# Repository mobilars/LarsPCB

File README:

These files are my PCB designs. Some of them are also copies of other PCBs that others have made. 

License: CC-BY-SA-NC

http://creativecommons.org/licenses/by-nc-sa/3.0/

More info on http://lars.roland.bz/

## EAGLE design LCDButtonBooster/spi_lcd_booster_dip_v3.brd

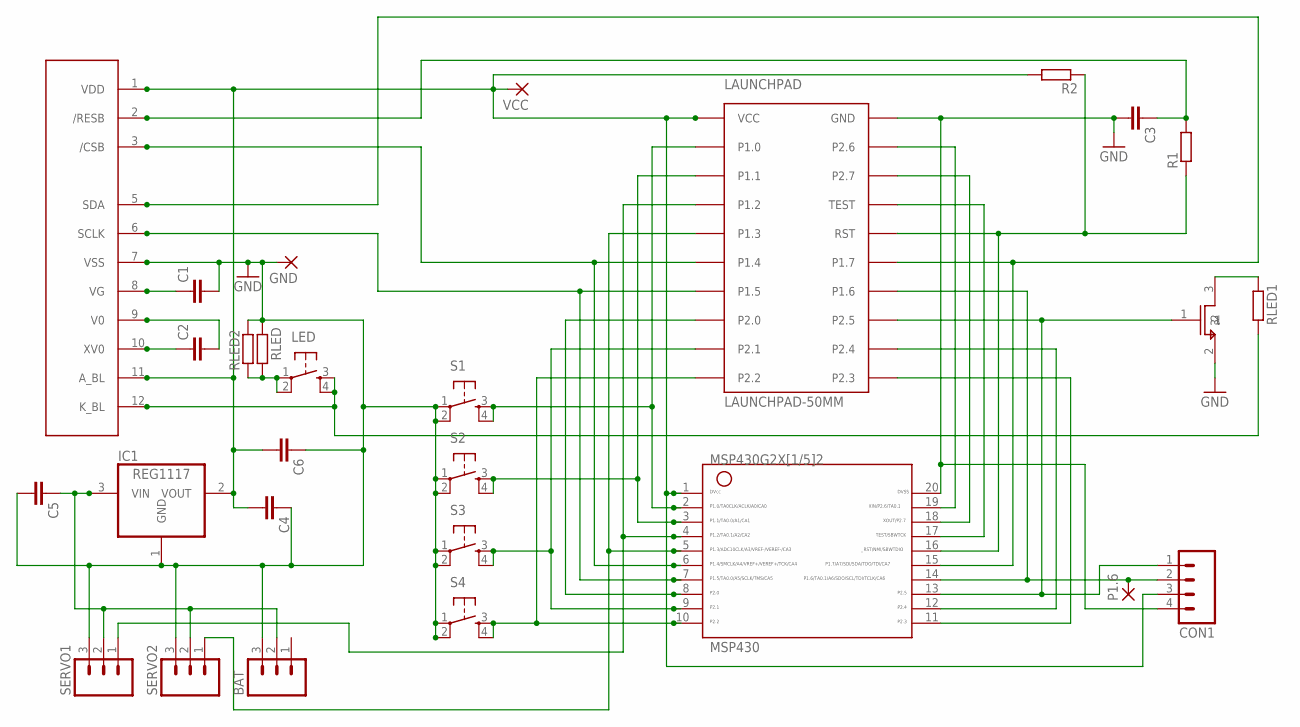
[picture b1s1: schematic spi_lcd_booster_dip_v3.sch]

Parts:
BAT: M03PTH; 1X03
C1, C2, C3, C4, C5, C6: CAP1206; 1206
CON1: M04PTH; 1X04
GND: 2,15/1,0
IC1: REG1117; SOT223
LAUNCHPAD: LAUNCHPAD-50MM
LED: TAC_SWITCHPTH; TACTILE-PTH
LEDSW: 2N7002PW; SOT323-R
MSP430: G2X[1/5]2---N20; N20
P1.6: 2,15/1,0
R1, R2: R-EU_R1206; R1206
RLED, RLED1: R-EU_R1206; R1206
RLED2: R-EU_0207/10; 0207/10
S1, S2, S3, S4: TAC_SWITCHPTH; TACTILE-PTH
SERVO1, SERVO2: M03PTH; 1X03
U$1: PE9665WRFPE9665WRF-WHOLE; PE9665WRF
VCC: 2,15/1,0

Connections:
CSB: LAUNCHPAD.P1.4, MSP430.6, U$1.3 (/CSB)
GND: BAT.3, C1.2, C3.2, C4.1, C5.2, C6.1, CON1.4, GND.1, IC1.1 (GND), LAUNCHPAD.GND, LEDSW.2, MSP430.20, RLED.1, RLED2.2, S1.1, S1.2, S2.1, S2.2, S3.1, S3.2, S4.1, S4.2, SERVO1.3, SERVO2.3, U$1.7 (VSS)
KBL: LED.3, LED.4, RLED1.2, U$1.12 (K_BL)
unnamed: C2.1, U$1.10 (XV0)
unnamed: C2.2, U$1.9 (V0)
unnamed: C1.1, U$1.8 (VG)
unnamed: LAUNCHPAD.P2.6, MSP430.19
unnamed: C3.1, R1.2, U$1.2 (/RESB)
unnamed: LAUNCHPAD.P2.7, MSP430.18
unnamed: LAUNCHPAD.RST, MSP430.16, R1.1, R2.1
unnamed: LAUNCHPAD.P1.7, MSP430.15, U$1.5 (SDA)
unnamed: LEDSW.3, RLED1.1
unnamed: LAUNCHPAD.TEST, MSP430.17
unnamed: LAUNCHPAD.P2.2, MSP430.10, S4.3, S4.4
unnamed: CON1.2, LAUNCHPAD.P1.6, MSP430.14, P1.6.1
unnamed: CON1.1, LAUNCHPAD.P2.5, LEDSW.1, MSP430.13
unnamed: LAUNCHPAD.P2.4, MSP430.12
unnamed: LAUNCHPAD.P2.3, MSP430.11
unnamed: LAUNCHPAD.P2.1, MSP430.9, S3.3, S3.4
unnamed: LAUNCHPAD.P1.5, MSP430.7, U$1.6 (SCLK)
unnamed: LAUNCHPAD.P2.0, MSP430.8
unnamed: LED.1, LED.2, RLED.2, RLED2.1
P1.0: LAUNCHPAD.P1.0, MSP430.2, S1.3, S1.4
P1.1: LAUNCHPAD.P1.1, MSP430.3, S2.3, S2.4
P1.2: LAUNCHPAD.P1.2, MSP430.4, SERVO1.1
P1.3: LAUNCHPAD.P1.3, MSP430.5, SERVO2.1
VBAT: BAT.2, C5.1, IC1.3 (VIN), SERVO1.2, SERVO2.2
VDD: C4.2, C6.2, CON1.3, IC1.2 (VOUT), LAUNCHPAD.VCC, MSP430.1, R2.2, U$1.1 (VDD), U$1.11 (A_BL), VCC.1

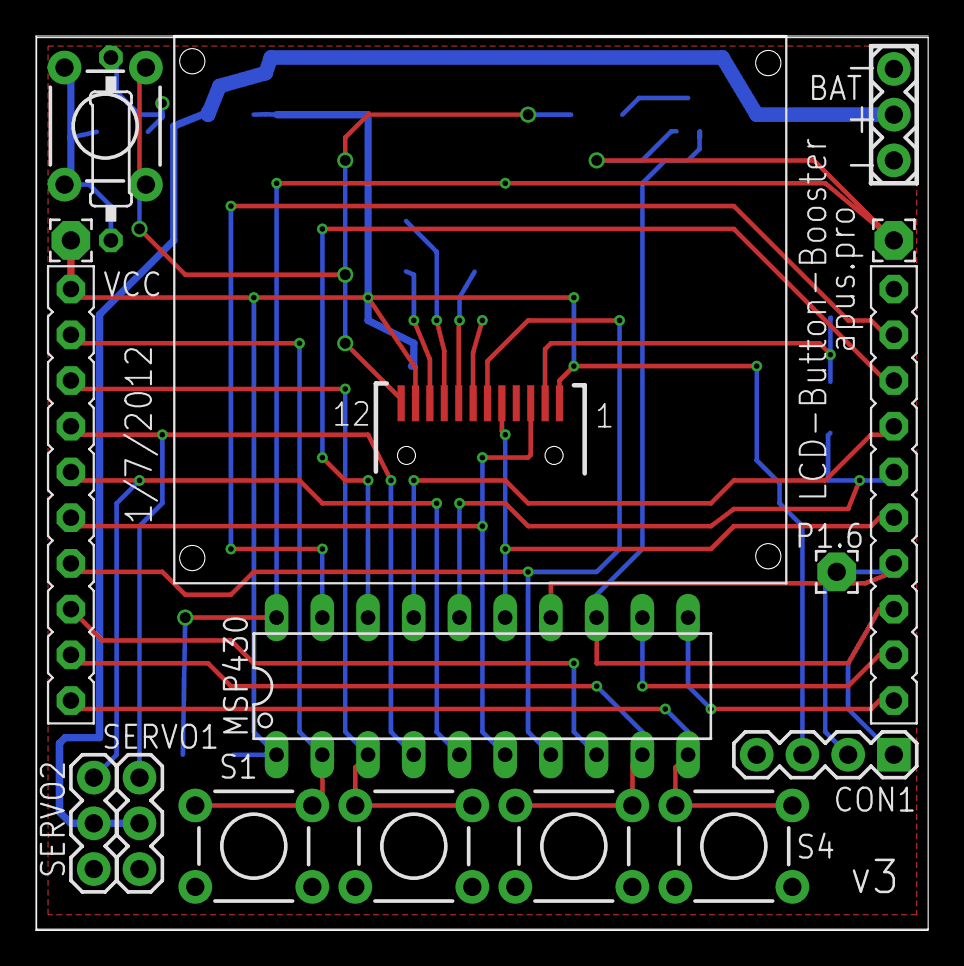
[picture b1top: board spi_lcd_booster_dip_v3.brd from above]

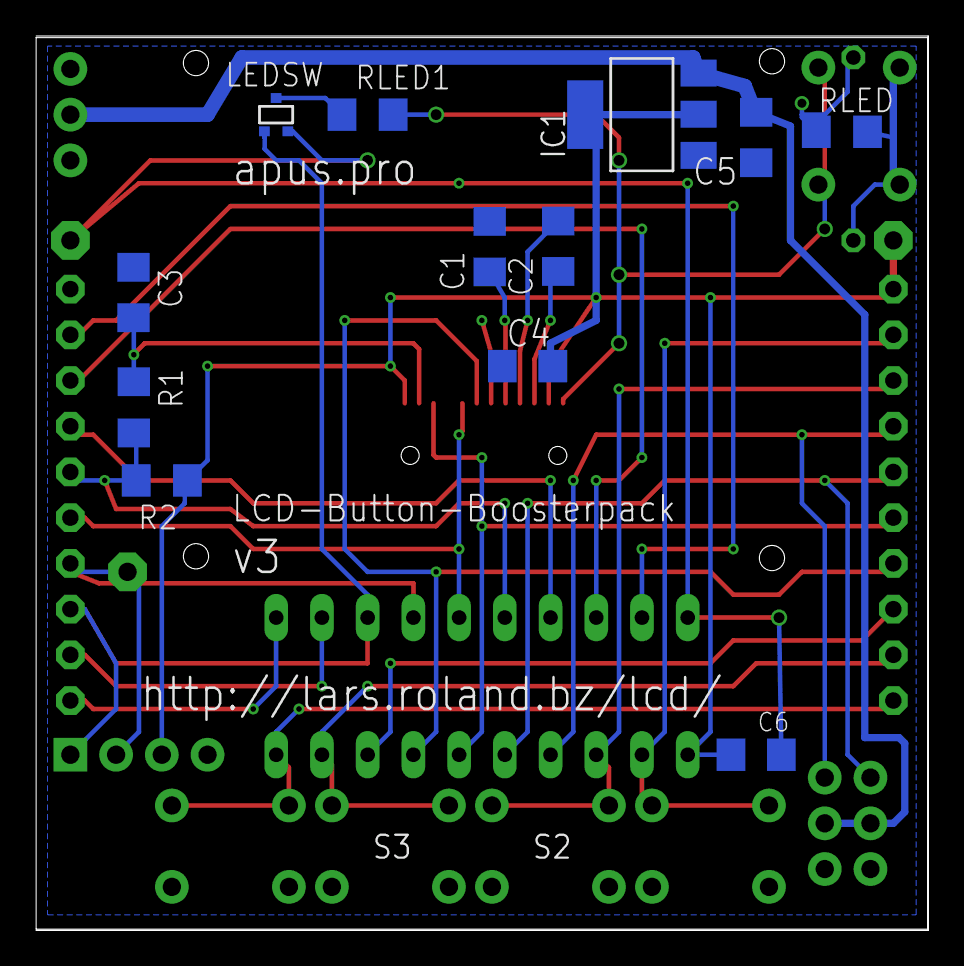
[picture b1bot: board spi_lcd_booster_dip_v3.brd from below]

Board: 2 copper layers, 49.6 x 49.7 mm, 28 parts (12 on the bottom side), 28 nets.

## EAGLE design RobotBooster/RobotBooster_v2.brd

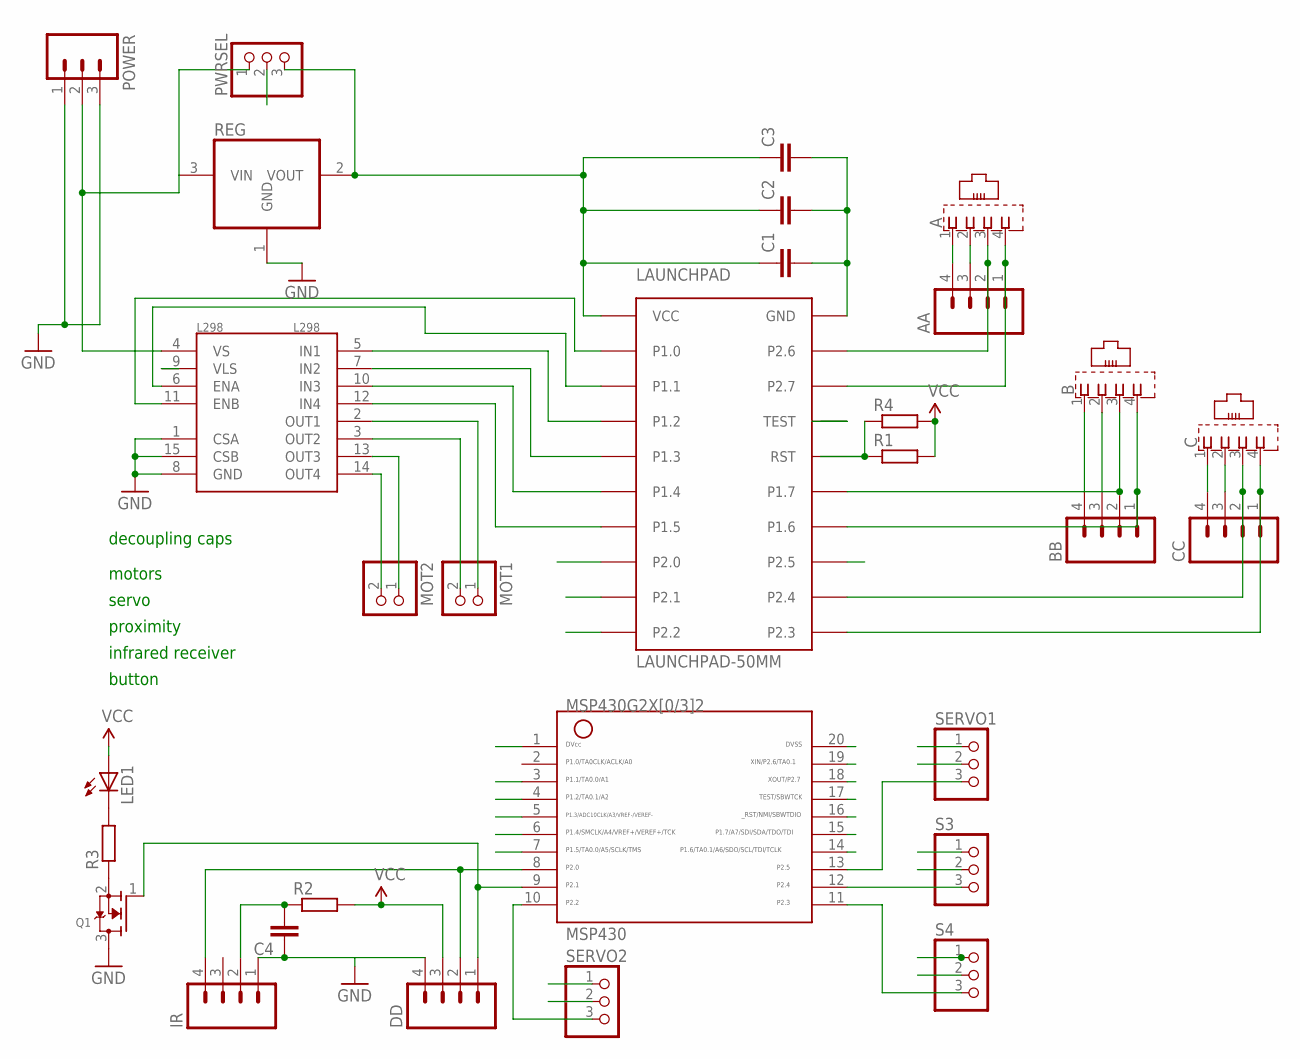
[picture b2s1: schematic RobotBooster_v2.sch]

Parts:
A: XRJK-S-01-6-4-0-9M2
AA: M04PTH; 1X04
B: XRJK-S-01-6-4-0-9M2
BB: M04PTH; 1X04
C: XRJK-S-01-6-4-0-9M2
C1, C2: C-EU025-030X050; C025-030X050
C3, C4: C-EUC1206; C1206
CC: M04PTH; 1X04
DD: M04PTH; 1X04
IR: M04PTH; 1X04
L298: L298; MULTIWATT15
LAUNCHPAD: LAUNCHPAD-50MM
LED1: LED5MM
MOT1, MOT2: PINHD-1X2; 1X02
MSP430: MSP430; N20
POWER: M03LONGPADS; 1X03_LONGPADS
PWRSEL: PINHD-1X3; 1X03
Q1: MOSFET-NREFLOW; SOT23
R1: R-EU_0207/10; 0207/10
R2, R3, R4: R-EU_R1206; R1206
REG: REG1117; SOT223
S3, S4: PINHD-1X3; 1X03
SERVO1, SERVO2: PINHD-1X3; 1X03

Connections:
GND: A.1, AA.4, B.1, BB.4, C.1, C1.2, C2.2, C3.2, C4.1, CC.4, DD.4, IR.1, L298.1 (CSA), L298.8 (GND), L298.15 (CSB), LAUNCHPAD.GND, MSP430.20, POWER.1, POWER.3, Q1.3 (D), REG.1 (GND), S3.1, S4.1, SERVO1.1, SERVO2.1
unnamed: L298.14 (OUT4), MOT2.2
unnamed: L298.13 (OUT3), MOT2.1
unnamed: L298.3 (OUT2), MOT1.2
unnamed: L298.2 (OUT1), MOT1.1
unnamed: C4.2, IR.2, R2.1
unnamed: Q1.2 (S), R3.1
unnamed: LED1.K (C), R3.2
unnamed: MSP430.13, SERVO1.3
P1.0: L298.11 (ENB), LAUNCHPAD.P1.0
P1.1: L298.6 (ENA), LAUNCHPAD.P1.1, MSP430.3
P1.2: L298.5 (IN1), LAUNCHPAD.P1.2, MSP430.4
P1.3: L298.7 (IN2), LAUNCHPAD.P1.3, MSP430.5
P1.4: L298.10 (IN3), LAUNCHPAD.P1.4, MSP430.6
P1.5: L298.12 (IN4), LAUNCHPAD.P1.5, MSP430.7
P1.6: B.4, BB.1, LAUNCHPAD.P1.6, MSP430.14
P1.7: B.3, BB.2, LAUNCHPAD.P1.7, MSP430.15
P2.0: DD.2, IR.4, LAUNCHPAD.P2.0, MSP430.8
P2.1: DD.1, LAUNCHPAD.P2.1, MSP430.9, Q1.1 (G)
P2.2: LAUNCHPAD.P2.2, MSP430.10, SERVO2.3
P2.3: C.4, CC.1, LAUNCHPAD.P2.3, MSP430.11, S4.3
P2.4: C.3, CC.2, LAUNCHPAD.P2.4, MSP430.12, S3.3
P2.5: LAUNCHPAD.P2.5
P2.6: A.3, AA.2, LAUNCHPAD.P2.6, MSP430.19
P2.7: A.4, AA.1, LAUNCHPAD.P2.7, MSP430.18
RST: LAUNCHPAD.RST, MSP430.16, R1.1, R4.1
TEST: LAUNCHPAD.TEST, MSP430.17
VBAT: L298.4 (VS), POWER.2, PWRSEL.1, REG.3 (VIN)
VCC: A.2, AA.3, B.2, BB.3, C.2, C1.1, C2.1, C3.1, CC.3, DD.3, L298.9 (VLS), LAUNCHPAD.VCC, LED1.A, MSP430.1, PWRSEL.3, R1.2, R2.2, R4.2, REG.2 (VOUT)
VSERV: PWRSEL.2, S3.2, S4.2, SERVO1.2, SERVO2.2

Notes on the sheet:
servo
proximity
infrared receiver
motors
button
decoupling caps

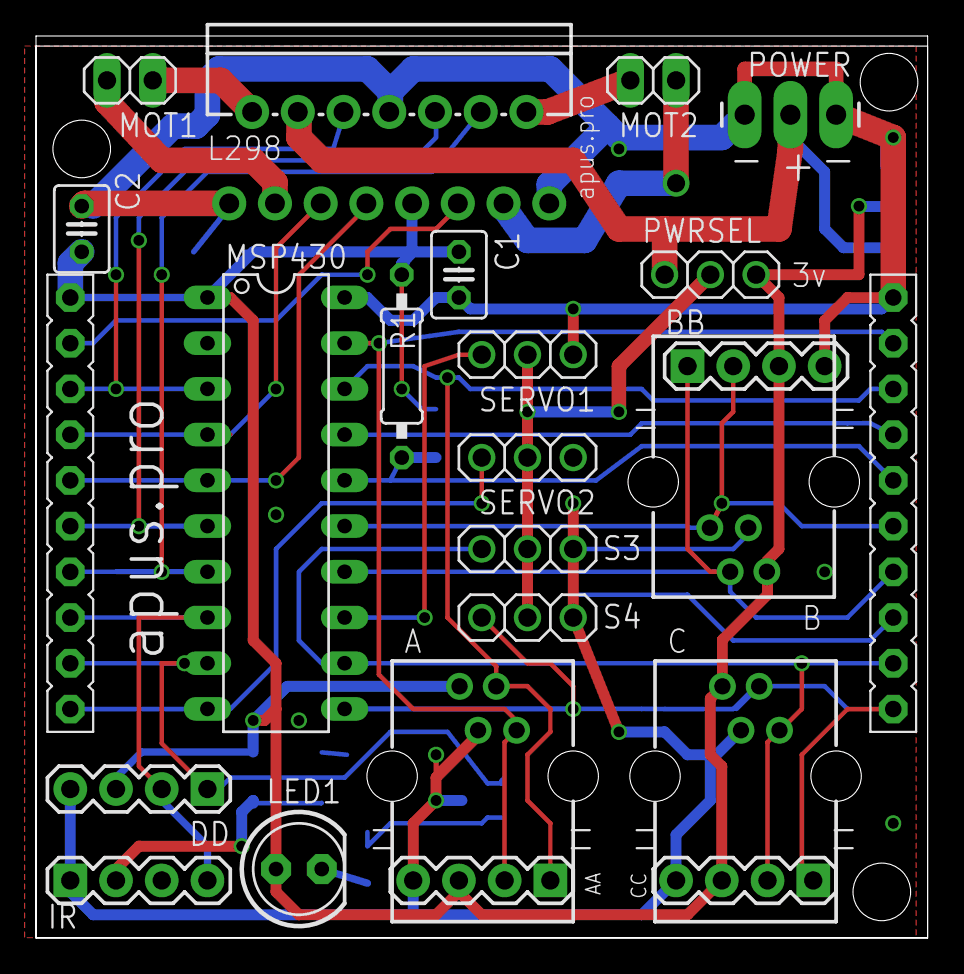
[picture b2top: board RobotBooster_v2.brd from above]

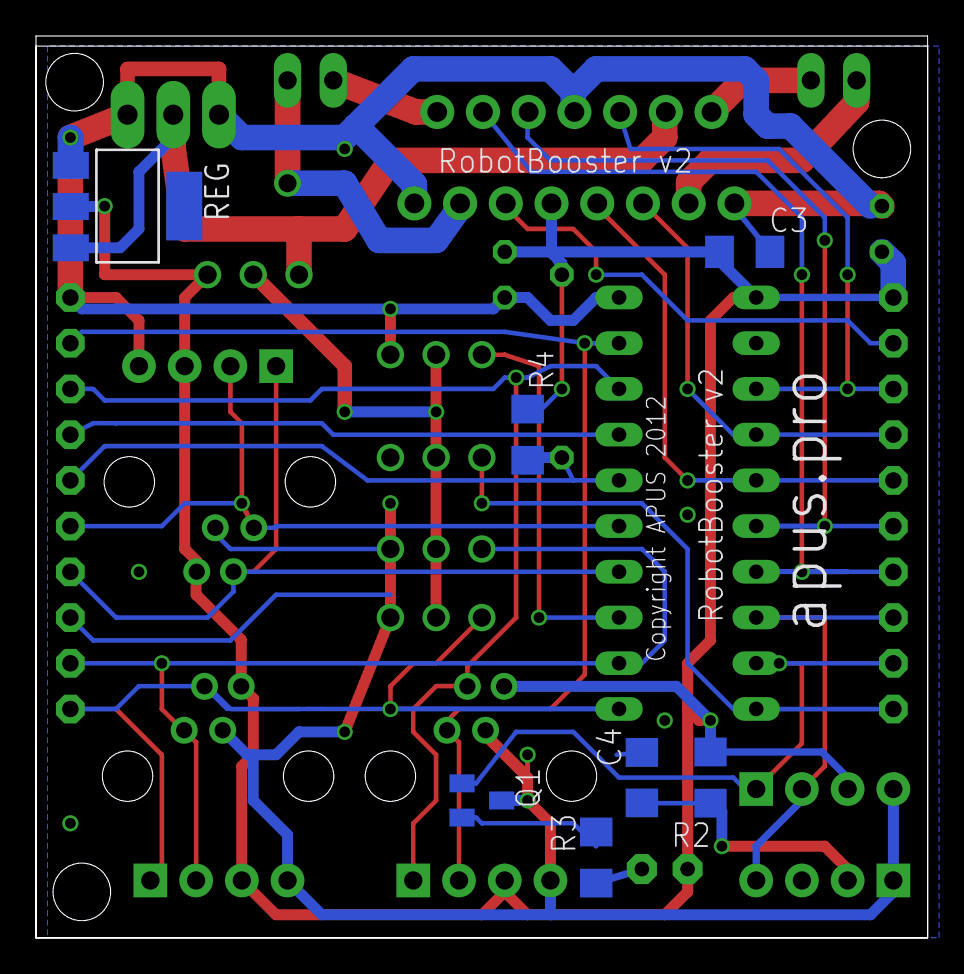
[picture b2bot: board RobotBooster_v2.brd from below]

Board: 2 copper layers, 49.5 x 50.1 mm, 30 parts (7 on the bottom side), 29 nets.

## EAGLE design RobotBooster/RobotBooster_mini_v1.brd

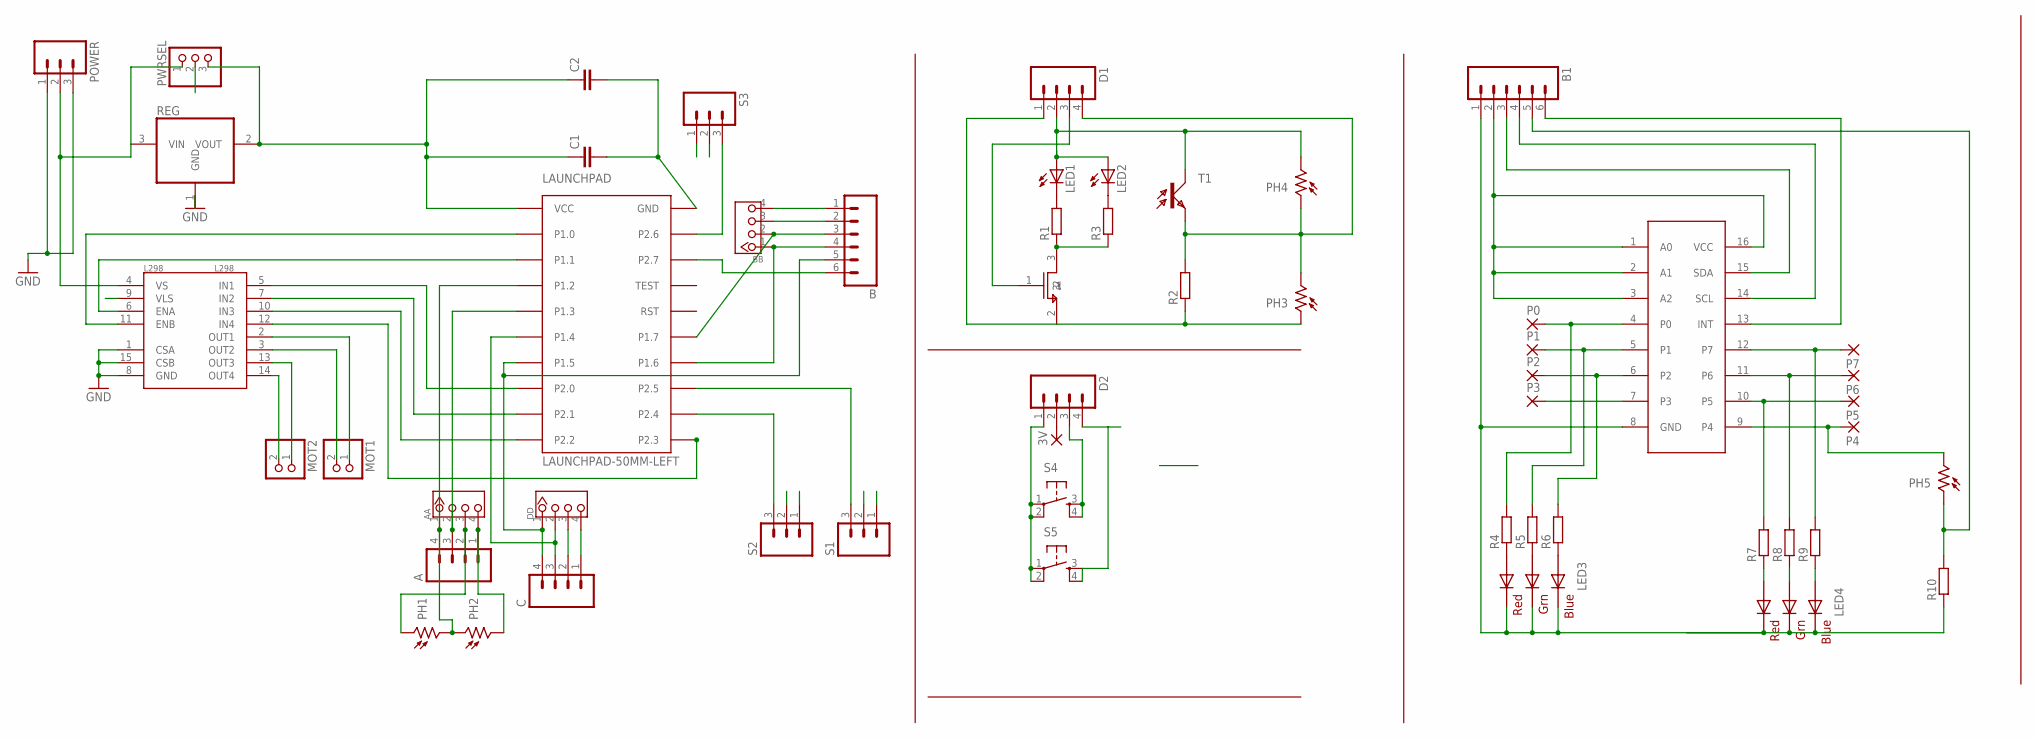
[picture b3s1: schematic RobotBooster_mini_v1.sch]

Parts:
3V: 1,6/0,8
A: M04PTH; 1X04
AA: TWIG-4P-2.0; 4P-2.0-W/O-BUCKLE
B, B1: M06SIP; 1X06
BB: TWIG-4P-2.0; 4P-2.0-W/O-BUCKLE
C: M04PTH; 1X04
C1: C-EU025-030X050; C025-030X050
C2: C-EUC1206; C1206
D1, D2: M04PTH; 1X04
DD: TWIG-4P-2.0; 4P-2.0-W/O-BUCKLE
FET: 2N7002PW; SOT323-R
L298: L298; MULTIWATT15
LAUNCHPAD: LAUNCHPAD-50MM-LEFT
LED1, LED2: LED5MM
LED3, LED4: RGBLED5050
MOT1, MOT2: PINHD-1X2; 1X02
P0, P1, P2, P3, P4, P5, P6, P7: 1,6/0,8
PH1, PH2, PH3, PH4, PH5: M9960_11A; M9960
POWER: M03LONGPADS; 1X03_LONGPADS
PWRSEL: PINHD-1X3; 1X03
R1, R2, R3: R-EU_R1206; R1206
R4, R5, R6, R7, R8, R9, R10: R-EU_R0805; R0805
REG: REG1117; SOT223
S1, S2, S3: M03PTH; 1X03
S4, S5: TAC_SWITCHPTH; TACTILE-PTH
T1: LPT80A
U$1: PCA9534DBR; SSOP16

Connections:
GND: A.1, AA.4, B.1, BB.4, C.1, C1.2, C2.2, DD.4, L298.1 (CSA), L298.8 (GND), L298.15 (CSB), LAUNCHPAD.GND, PH2.2, POWER.1, POWER.3, REG.1 (GND), S1.1, S2.1, S3.1
unnamed: L298.14 (OUT4), MOT2.2
unnamed: L298.13 (OUT3), MOT2.1
unnamed: L298.3 (OUT2), MOT1.2
unnamed: L298.2 (OUT1), MOT1.1
unnamed: D1.1, FET.2, PH3.1, R2.1
unnamed: FET.3, R1.1, R3.1
unnamed: LED1.K (C), R1.2
unnamed: A.4, AA.1, LAUNCHPAD.P1.2, PH1.2, PH2.1
unnamed: L298.5 (IN1), LAUNCHPAD.P2.0
unnamed: C.3, DD.2, LAUNCHPAD.P1.4
unnamed: D1.3, FET.1
unnamed: D1.4, PH3.2, PH4.1, R2.2, T1.E
unnamed: B.3, BB.2, LAUNCHPAD.P1.7
unnamed: B.4, BB.1, LAUNCHPAD.P1.6
unnamed: A.3, AA.2, LAUNCHPAD.P1.3
unnamed: LAUNCHPAD.P2.4, S2.3
unnamed: LAUNCHPAD.P2.5, S1.3
unnamed: B.5, C.4, DD.1, LAUNCHPAD.P1.5
unnamed: D1.2, LED1.A, LED2.A, PH4.2, T1.C
unnamed: LED2.K (C), R3.2
unnamed: P6.1, R8.2, U$1.11 (P6)
unnamed: P3.1, U$1.7 (P3)
unnamed: B.6, LAUNCHPAD.P2.7
unnamed: D2.1, S4.1, S4.2, S5.1, S5.2
unnamed: 3V.1, D2.2
unnamed: LAUNCHPAD.P2.6, S3.3
unnamed: D2.3, S4.3, S4.4
unnamed: D2.4, S5.3, S5.4
unnamed: B1.2, U$1.1 (A0), U$1.2 (A1), U$1.3 (A2), U$1.16 (VCC)
unnamed: B1.1, LED3.4 (BLUE_C), LED3.5 (RED_C), LED3.6 (GREEN_C), LED4.4 (BLUE_C), LED4.5 (RED_C), LED4.6 (GREEN_C), R10.1, U$1.8 (GND)
unnamed: B1.3, U$1.15 (SDA)
unnamed: B1.4, U$1.14 (SCL)
unnamed: P7.1, R9.2, U$1.12 (P7)
unnamed: LED3.2 (RED_A), R4.1
unnamed: LED3.1 (GREEN_A), R5.1
unnamed: LED3.3 (BLUE_A), R6.1
unnamed: B1.6, U$1.13 (INT)
unnamed: LED4.2 (RED_A), R7.1
unnamed: LED4.1 (GREEN_A), R8.1
unnamed: LED4.3 (BLUE_A), R9.1
unnamed: P0.1, R4.2, U$1.4 (P0)
unnamed: P1.1, R5.2, U$1.5 (P1)
unnamed: P2.1, R6.2, U$1.6 (P2)
unnamed: B1.5, PH5.1, R10.2
unnamed: P4.1, PH5.2, U$1.9 (P4)
unnamed: P5.1, R7.2, U$1.10 (P5)
P1.0: L298.11 (ENB), LAUNCHPAD.P1.0
P1.1: L298.6 (ENA), LAUNCHPAD.P1.1
P1.3: L298.7 (IN2), LAUNCHPAD.P2.1
P1.4: L298.10 (IN3), LAUNCHPAD.P2.2
P1.5: L298.12 (IN4), LAUNCHPAD.P2.3
VBAT: L298.4 (VS), POWER.2, PWRSEL.1, REG.3 (VIN)
VCC: A.2, AA.3, B.2, BB.3, C.2, C1.1, C2.1, DD.3, L298.9 (VLS), LAUNCHPAD.VCC, PH1.1, PWRSEL.3, REG.2 (VOUT)
VSERV: PWRSEL.2, S1.2, S2.2, S3.2

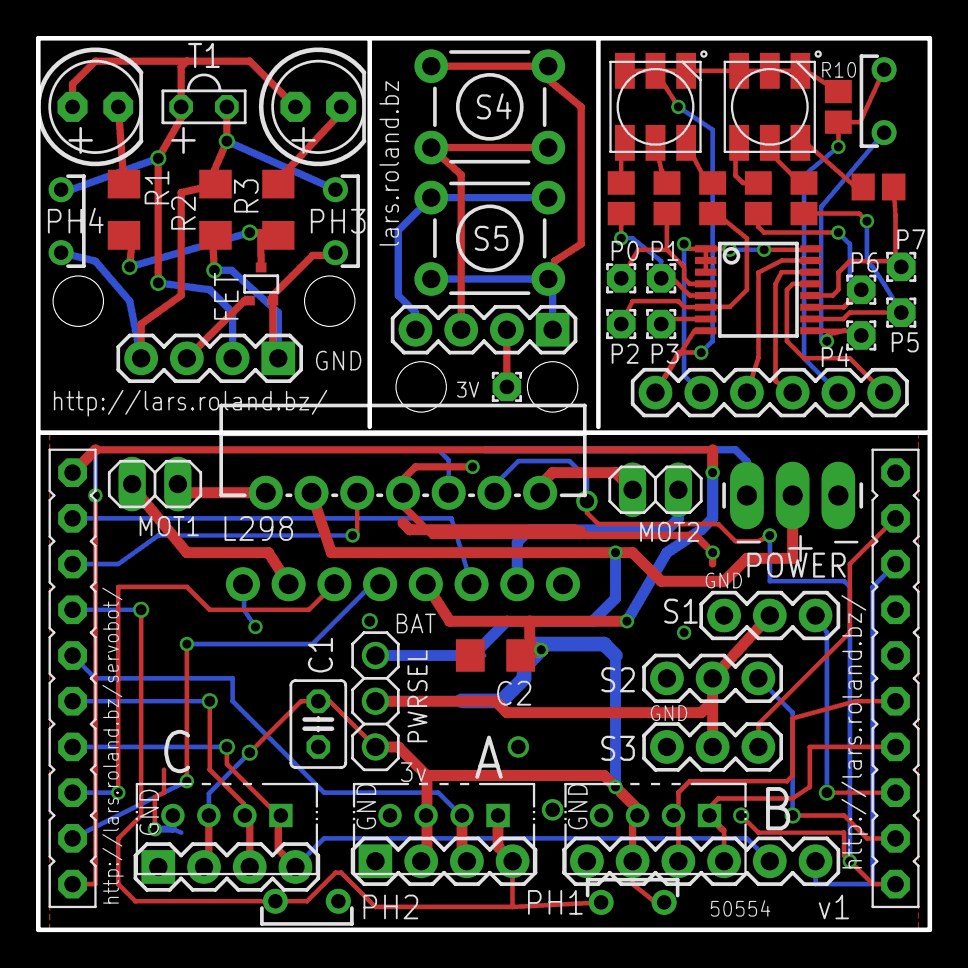
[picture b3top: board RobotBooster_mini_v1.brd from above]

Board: 2 copper layers, 49.5 x 49.5 mm, 54 parts (1 on the bottom side), 55 nets.

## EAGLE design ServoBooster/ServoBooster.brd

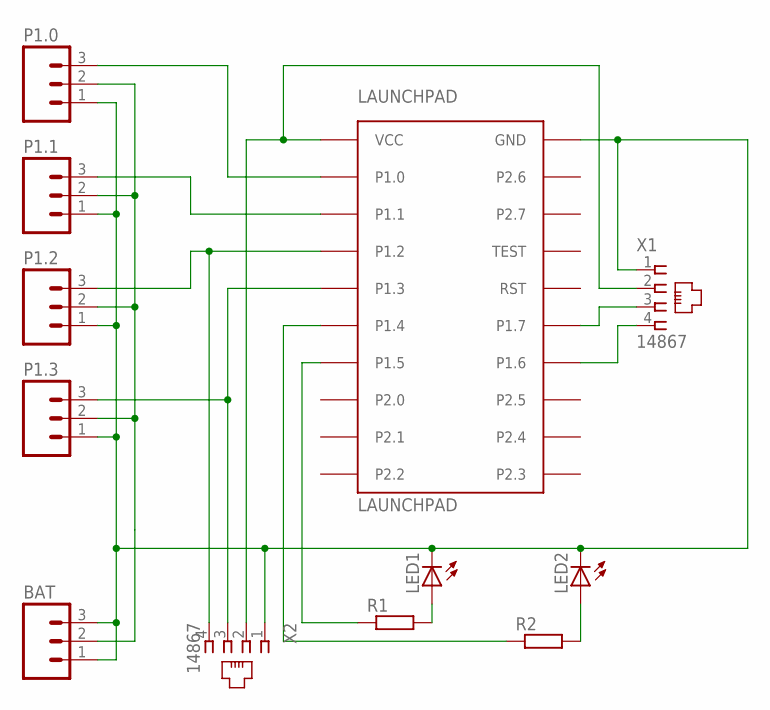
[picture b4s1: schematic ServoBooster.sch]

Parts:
BAT: M03PTH; 1X03
LAUNCHPAD: LAUNCHPAD
LED1, LED2: LED5MM
P1.0, P1.1, P1.2, P1.3: M03PTH; 1X03
R1, R2: R-EU_0207/10; 0207/10
X1, X2: 14867

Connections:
GND: BAT.1, BAT.2, BAT.3, LAUNCHPAD.GND, LED1.K (C), LED2.K (C), P1.0.1, P1.1.1, P1.2.1, P1.3.1, X1.1, X2.1
unnamed: LAUNCHPAD.P1.7, X1.3
unnamed: LAUNCHPAD.P1.0, P1.0.3
unnamed: LAUNCHPAD.P1.1, P1.1.3
unnamed: LAUNCHPAD.P1.2, P1.2.3, X2.4
unnamed: LAUNCHPAD.P1.3, P1.3.3, X2.3
unnamed: LAUNCHPAD.P1.6, X1.4
unnamed: LED1.A, R1.2
unnamed: LED2.A, R2.2
unnamed: LAUNCHPAD.P1.5, R1.1
unnamed: LAUNCHPAD.P1.4, R2.1
VBAT: P1.0.2, P1.1.2, P1.2.2, P1.3.2
VCC: LAUNCHPAD.VCC, X1.2, X2.2

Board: 2 copper layers, 12 parts (0 on the bottom side), 13 nets, no tracks yet.

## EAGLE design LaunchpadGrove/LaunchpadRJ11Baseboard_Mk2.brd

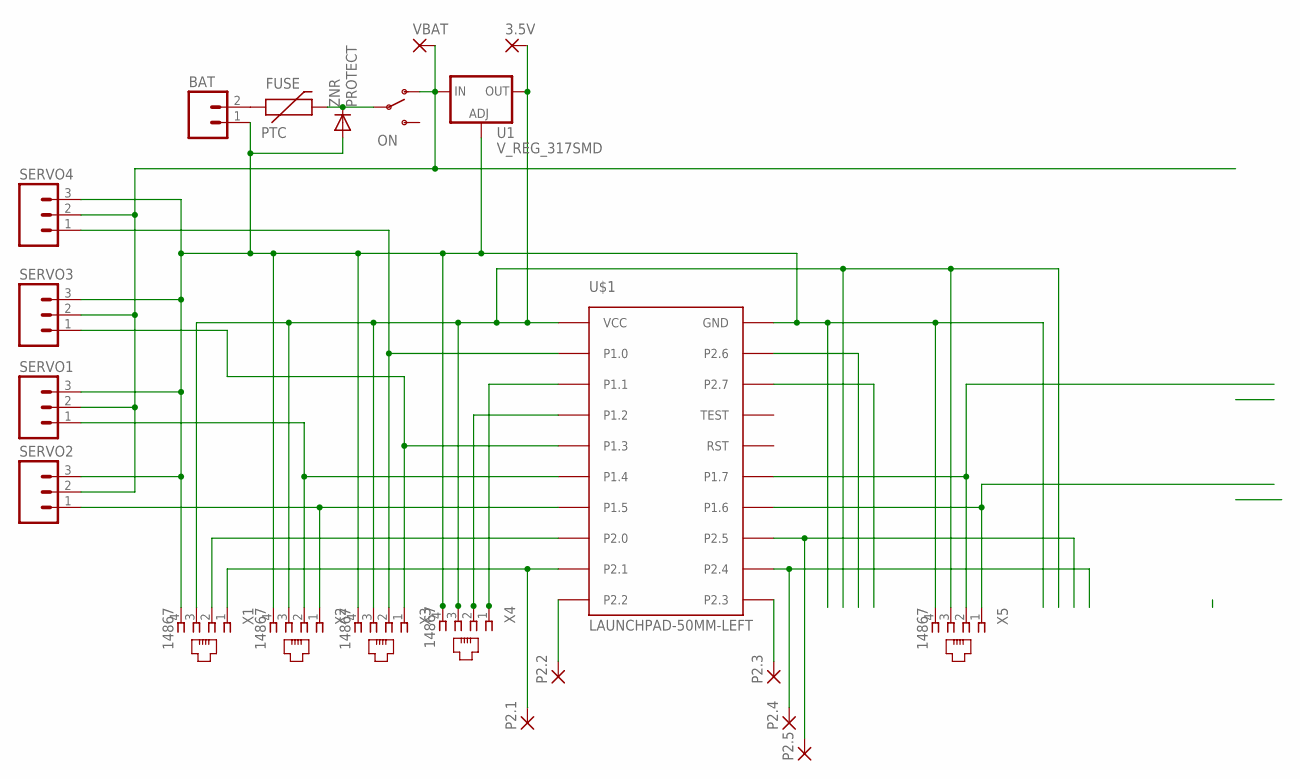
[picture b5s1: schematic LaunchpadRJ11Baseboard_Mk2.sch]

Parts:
3.5V: 2,15/1,0
BAT: M02PTH; 1X02
FUSE: PTC
ON: SWITCH-SPSTPTH; SWITCH-SPDT
P2.1, P2.2, P2.3, P2.4, P2.5: 2,15/1,0
SERVO1, SERVO2, SERVO3, SERVO4: M03PTH; 1X03
U1: V_REG_317SMD; SOT223
U$1: LAUNCHPAD-50MM-LEFT
VBAT: 2,15/1,0
X1, X2, X3, X4, X5: 14867
ZNR: PROTECT; DO41-10

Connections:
GND: BAT.1, SERVO1.3, SERVO2.3, SERVO3.3, SERVO4.3, U1.1 (ADJ), U$1.GND, X1.4, X2.4, X3.4, X4.4, X5.4, ZNR.A
unnamed: U$1.P1.2, X4.2
unnamed: BAT.2, FUSE.P$1 (1)
unnamed: SERVO4.1, U$1.P1.0, X3.2
unnamed: U$1.P1.1, X4.1
unnamed: SERVO3.1, U$1.P1.3, X3.1
unnamed: SERVO1.1, U$1.P1.4, X2.2
unnamed: SERVO2.1, U$1.P1.5, X2.1
unnamed: U$1.P1.7, X5.2
unnamed: U$1.P1.6, X5.1
unnamed: P2.5.1, U$1.P2.5
unnamed: P2.4.1, U$1.P2.4
unnamed: U$1.P2.0, X1.2
unnamed: FUSE.P$2 (2), ON.2, ZNR.C
unnamed: P2.2.1, U$1.P2.2
unnamed: P2.1.1, U$1.P2.1, X1.1
unnamed: P2.3.1, U$1.P2.3
VBAT: ON.1 (O), SERVO1.2, SERVO2.2, SERVO3.2, SERVO4.2, U1.3 (IN), VBAT.1
VCC: 3.5V.1, U1.2 (OUT), U$1.VCC, X1.3, X2.3, X3.3, X4.3, X5.3

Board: 2 copper layers, 22 parts (0 on the bottom side), 19 nets, no tracks yet.

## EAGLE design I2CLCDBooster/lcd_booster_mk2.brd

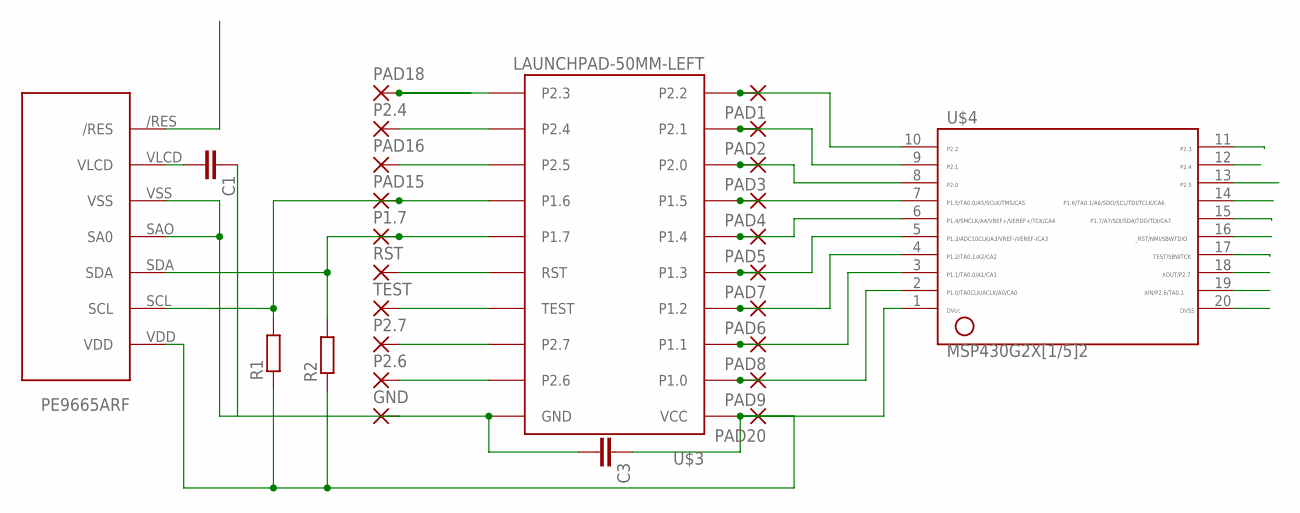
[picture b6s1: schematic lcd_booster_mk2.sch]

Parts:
C1, C3: C-EUC1206; C1206
GND: 1,6/0,9
P1.7, P2.4, P2.6, P2.7: 1,6/0,9
PAD1, PAD2, PAD3, PAD4, PAD5, PAD6, PAD7, PAD8, PAD9, PAD15, PAD16, PAD18, PAD20: 1,6/0,9
R1, R2: R-EU_M1206; M1206
RST: 1,6/0,9
TEST: 1,6/0,9
U$2: PE9665ARF
U$3: LAUNCHPAD-50MM-LEFT
U$4: G2X[1/5]2---PW20; PW20

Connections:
GND: C1.1, C3.2, GND.1, U$2.SAO (SA0), U$2.VSS, U$3.GND, U$4.20
unnamed: PAD1.1, U$3.P2.2, U$4.10
unnamed: C1.2, U$2.VLCD
unnamed: PAD2.1, U$3.P2.1, U$4.9
unnamed: PAD3.1, U$3.P2.0, U$4.8
unnamed: PAD4.1, U$3.P1.5, U$4.7
unnamed: PAD5.1, U$3.P1.4, U$4.6
unnamed: PAD6.1, U$3.P1.2, U$4.4
unnamed: PAD8.1, U$3.P1.1, U$4.3
unnamed: PAD9.1, U$3.P1.0, U$4.2
unnamed: C3.1, PAD20.1, R1.1, R2.1, U$2.VDD, U$3.VCC, U$4.1
unnamed: PAD7.1, U$3.P1.3, U$4.5
P1.6: PAD15.1, R1.2, U$2.SCL, U$3.P1.6, U$4.14
P1.7: P1.7.1, R2.2, U$2.SDA, U$3.P1.7, U$4.15
P2.3: PAD18.1, U$3.P2.3, U$4.11
P2.4: P2.4.1, U$3.P2.4, U$4.12
P2.5: PAD16.1, U$3.P2.5, U$4.13
P2.6: P2.6.1, U$3.P2.6, U$4.19
P2.7: P2.7.1, U$3.P2.7, U$4.18
RST: RST.1, U$3.RST, U$4.16
TEST: TEST.1, U$3.TEST, U$4.17

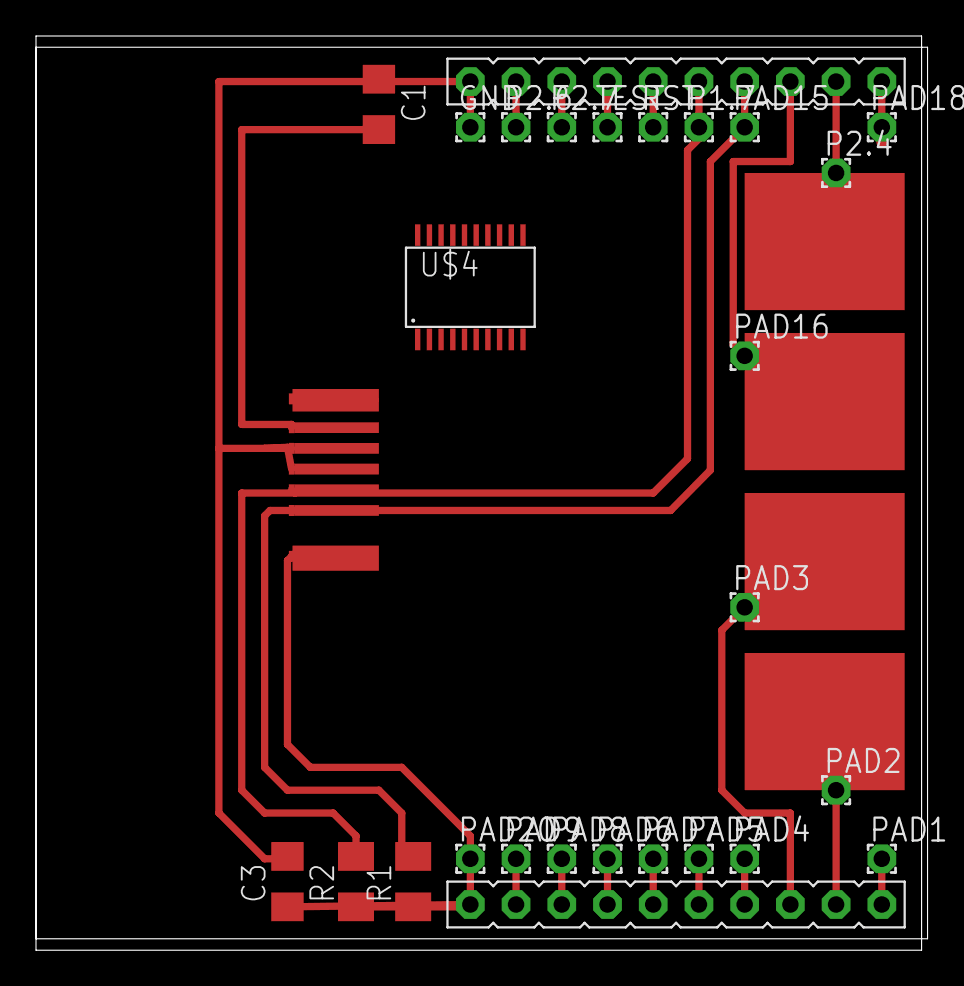
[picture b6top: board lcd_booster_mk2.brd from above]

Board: 2 copper layers, 49.5 x 50.8 mm, 27 parts (0 on the bottom side), 21 nets.

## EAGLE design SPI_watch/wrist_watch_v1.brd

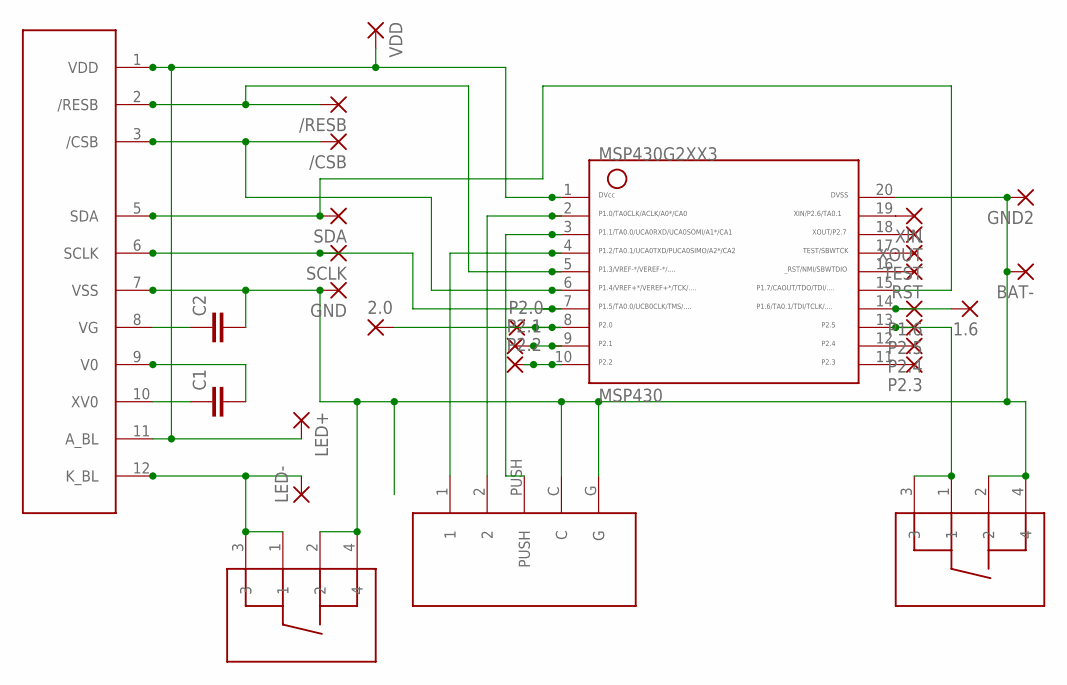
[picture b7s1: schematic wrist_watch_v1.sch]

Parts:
1.6, 2.0: 1,6/0,9
/CSB: 1,6/0,9
/RESB: 1,6/0,9
BAT-: SMD5; SMD2,54-5,08
C1, C2: CAP0805; 0805
GND: 1,6/0,9
GND2: SMD2; SMD1,27-2,54
LED+: 1,6/0,9
LED-: 1,6/0,9
MSP430: G2XX3---PW20; PW20
P1.6, P2.0, P2.1, P2.2, P2.3, P2.4, P2.5: SMD2; SMD1,27-2,54
RST: 1,6/0,9
SCLK: 1,6/0,9
SDA: 1,6/0,9
TEST: 1,6/0,9
U$1: PE9665WRFPE9665WRF-WHOLE; PE9665WRF
U$2, U$4: MCPTCF-V
U$3: MCPL3-BC-V
VDD: 1,6/0,9
XIN: SMD2; SMD1,27-2,54
XOUT: SMD2; SMD1,27-2,54

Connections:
C2: C2.1, U$1.8 (VG)
GND: BAT-.1, C2.2, GND.1, GND2.1, MSP430.20, U$1.7 (VSS), U$2.2, U$2.4, U$3.C, U$3.G, U$4.2, U$4.4; also elsewhere on the board
LED-: LED-.1, U$1.12 (K_BL), U$2.1, U$2.3
unnamed: C1.1, U$1.10 (XV0)
unnamed: C1.2, U$1.9 (V0)
unnamed: MSP430.19, XIN.1
unnamed: MSP430.3, U$3.PUSH
unnamed: MSP430.17, TEST.1
unnamed: MSP430.18, XOUT.1
unnamed: MSP430.7, SCLK.1, U$1.6 (SCLK)
unnamed: MSP430.15, SDA.1, U$1.5 (SDA)
unnamed: /CSB.1, MSP430.6, U$1.3 (/CSB)
unnamed: /RESB.1, MSP430.5, U$1.2 (/RESB)
unnamed: MSP430.4, U$3.1
unnamed: 1.6.1, MSP430.14, P1.6.1
unnamed: MSP430.2, U$3.2
unnamed: MSP430.13, P2.5.1, U$4.1, U$4.3
unnamed: MSP430.12, P2.4.1
unnamed: MSP430.11, P2.3.1
unnamed: MSP430.9, P2.1.1
unnamed: MSP430.10, P2.2.1
unnamed: 2.0.1, MSP430.8, P2.0.1

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
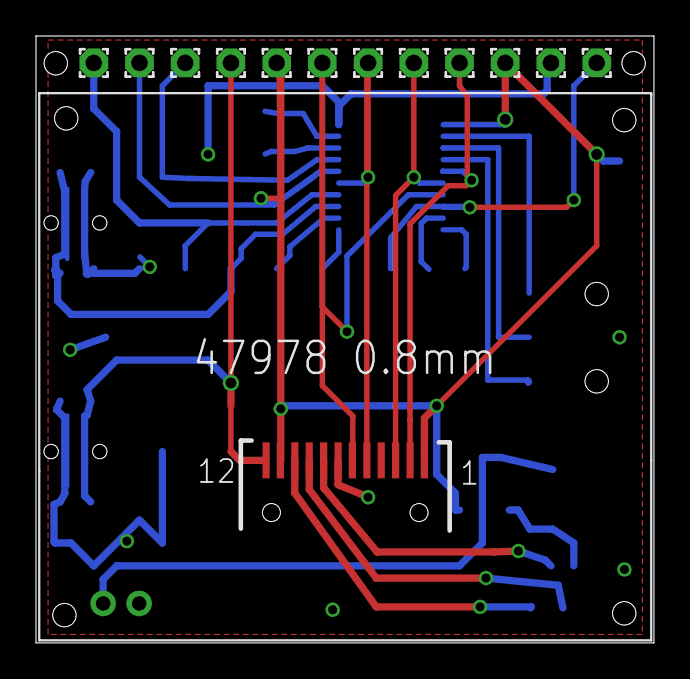
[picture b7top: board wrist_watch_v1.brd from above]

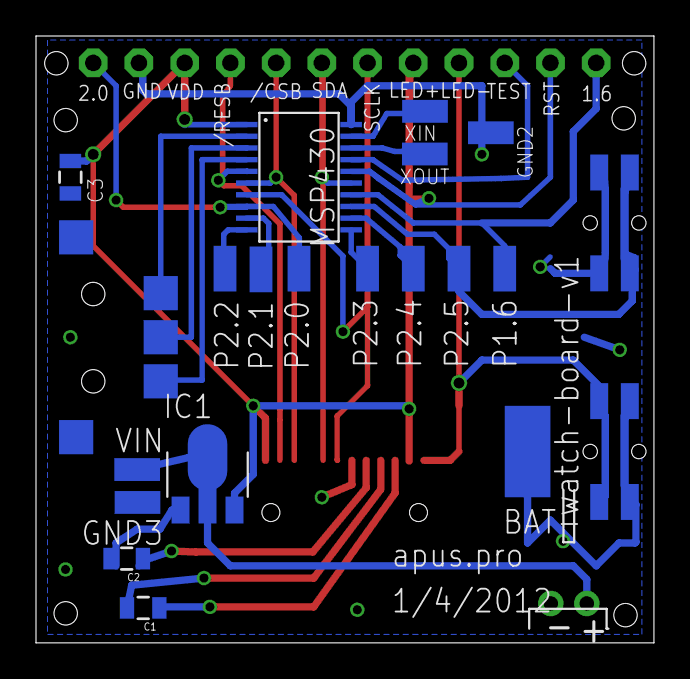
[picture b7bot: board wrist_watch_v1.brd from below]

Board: 2 copper layers, 34.3 x 33.7 mm, 35 parts (22 on the bottom side), 24 nets.

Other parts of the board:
C3: 0805
CN1: JST-PH-2-THM-RA
GND3: SMD1,27-2,54
IC1: MCP170312MB; SOT89
VIN: SMD1,27-2,54

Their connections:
GND: C3.1, CN1.2, GND3.1, IC1.1; also elsewhere on the board
unnamed: CN1.1, IC1.2@1, VIN.1

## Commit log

2012-01-21 Adding CC-BY-SA-NC License
2012-01-22 SW i2c P1.4 P1.5 and LCDRST connected to chip RST
2012-01-22 First version (not finished)
2012-01-23 Added switch, vbat, cct protection etc
2012-01-23 Space for larger zener
2012-03-31 Various boards for the SPI LCD display
2012-03-31 Removed some files that should be ignored
2012-03-31 Removed wrong, added right
2012-05-07 Added SPI LCD Displays
2012-08-07 Various changes

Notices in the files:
RobotBooster/RobotBooster_mini_v1.brd:
Copyright APUS 2012
parts and their libraries:
SparkFun: Licensing: CC v3.0 Share-Alike You are welcome to use this library for commercial purposes.
